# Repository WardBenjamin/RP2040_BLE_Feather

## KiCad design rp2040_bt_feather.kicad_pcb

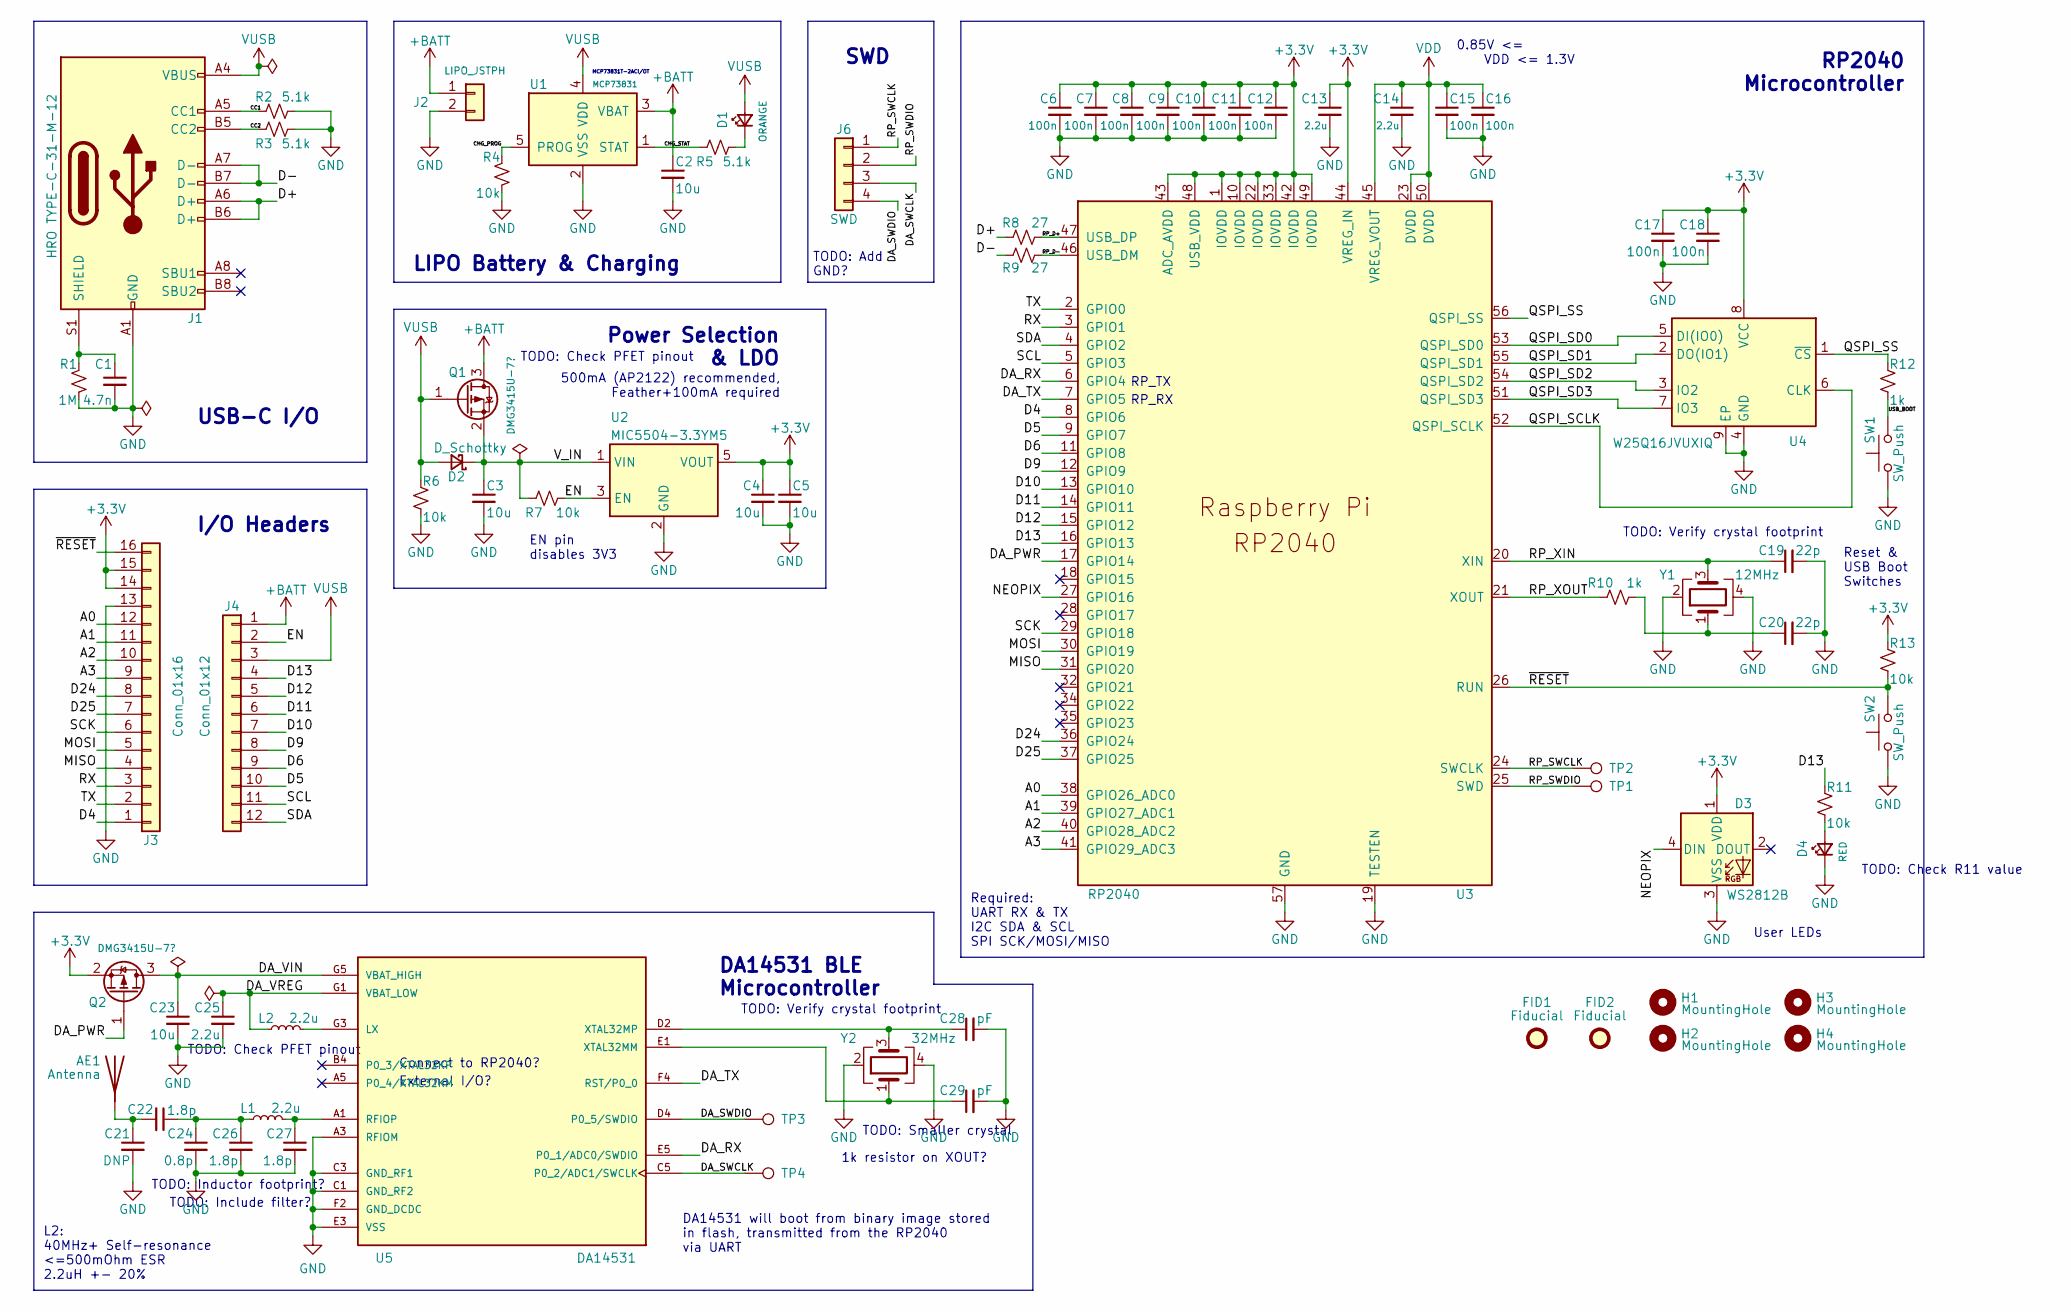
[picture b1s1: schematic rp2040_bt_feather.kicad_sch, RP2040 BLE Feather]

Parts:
AE1: Antenna
C1: 4.7n; C_0603_1608Metric
C2, C3, C4, C5: 10u; C_0805_2012Metric
C6, C7, C8, C9, C10, C11, C12, C15, C16, C17, C18: 100n; C_0603_1608Metric
C13, C14, C25: 2.2u; C_0603_1608Metric
C19, C20: 22p; C_0603_1608Metric
C21: DNP; C_0603_1608Metric
C22, C26, C27: 1.8p; C_0603_1608Metric
C23: 10u; C_0603_1608Metric
C24: 0.8p; C_0603_1608Metric
C28, C29: pF; C_0603_1608Metric
D1: ORANGE; D_0603_1608Metric; MPN ‎LTST-C190KFKT
D2: D_Schottky; D_SOD-123F
D3: WS2812B; LED_WS2812B_PLCC4_5.0x5.0mm_P3.2mm
D4: RED; D_0603_1608Metric
FID1, FID2: Fiducial; Fiducial_1mm_Mask2mm
H1, H2, H3, H4: MountingHole; MountingHole_2.5mm
J1: HRO TYPE-C-31-M-12; USB_C_Receptacle_HRO_TYPE-C-31-M-12
J2: LIPO_JSTPH; JST_PH_S2B-PH-SM4-TB_1x02-1MP_P2.00mm_Horizontal
J3: Conn_01x16; PinHeader_1x16_P2.54mm_Vertical
J4: Conn_01x12; PinHeader_1x12_P2.54mm_Vertical
J6: SWD; PinHeader_1x04_P2.54mm_Vertical
L1: 2.2u; L_0603_1608Metric
L2: 2.2u; L_0805_2012Metric
Q1, Q2: DMG3415U-7?; SOT-23
R1: 1M; R_0603_1608Metric
R2, R3, R5: 5.1k; R_0603_1608Metric
R4, R6, R7, R11, R13: 10k; R_0603_1608Metric
R8, R9: 27; R_0603_1608Metric
R10, R12: 1k; R_0603_1608Metric
SW1, SW2: SW_Push; SW_SPST_PTS830
TP1, TP3: SWDIO; TestPoint_THTPad_1.0x1.0mm_Drill0.5mm
TP2, TP4: SWCLK; TestPoint_THTPad_1.0x1.0mm_Drill0.5mm
U1: MCP73831; SOT-23-5; MPN MCP73831T-2ACI/OT
U2: MIC5504-3.3YM5; SOT-23-5
U3: RP2040; RP2040-QFN-56
U4: W25Q16JVUXIQ; WSON-8-1EP_6x5mm_P1.27mm_EP3.4x4.3mm
U5: DA14531; XCVR_DA14531-00000OG2; PARTREV 2.1
Y1: 12MHz; Crystal_SMD_2016-4Pin_2.0x1.6mm
Y2: 32MHz; Crystal_SMD_2016-4Pin_2.0x1.6mm; MPN ECS-320-8-37B-CKY-TR

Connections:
+3V3: C4.1, C5.1, C6.1, C7.1, C8.1, C9.1, C10.1, C11.1, C12.1, C13.1, C17.1, C18.1, D3.1 (VDD), J3.14, J3.15, Q2.2 (S), R13.1, U2.5 (VOUT), U3.1 (IOVDD), U3.10 (IOVDD), U3.22 (IOVDD), U3.33 (IOVDD), U3.42 (IOVDD), U3.43 (ADC_AVDD), U3.44 (VREG_IN), U3.48 (USB_VDD), U3.49 (IOVDD), U4.8 (VCC)
+BATT: C2.1, J2.1, J4.1, Q1.3 (D), U1.3 (VBAT)
/A0: J3.12, U3.38 (GPIO26_ADC0)
/A1: J3.11, U3.39 (GPIO27_ADC1)
/A2: J3.10, U3.40 (GPIO28_ADC2)
/A3: J3.9, U3.41 (GPIO29_ADC3)
/CC1: J1.A5 (CC1), R2.1
/CC2: J1.B5 (CC2), R3.1
/CHG_PROG: R4.1, U1.5 (PROG)
/CHG_STAT: R5.1, U1.1 (STAT)
/D4: J3.1, U3.8 (GPIO6)
/D5: J4.10, U3.9 (GPIO7)
/D6: J4.9, U3.11 (GPIO8)
/D9: J4.8, U3.12 (GPIO9)
/D10: J4.7, U3.13 (GPIO10)
/D11: J4.6, U3.14 (GPIO11)
/D12: J4.5, U3.15 (GPIO12)
/D13: J4.4, R11.1, U3.16 (GPIO13)
/D24: J3.8, U3.36 (GPIO24)
/D25: J3.7, U3.37 (GPIO25)
/D+: J1.A6 (D+), J1.B6 (D+), R8.1; also elsewhere on the board
/D-: J1.A7 (D-), J1.B7 (D-), R9.1; also elsewhere on the board
/DA_PWR: Q2.1 (G), U3.17 (GPIO14)
/DA_RX: U3.6 (GPIO4), U5.E5 (P0_1/ADC0/SWDIO)
/DA_SWCLK: J6.3, TP4.1, U5.C5 (P0_2/ADC1/SWCLK)
/DA_SWDIO: J6.4, TP3.1, U5.D4 (P0_5/SWDIO); also elsewhere on the board
/DA_TX: U3.7 (GPIO5), U5.F4 (RST/P0_0)
/DA_VIN: C23.1, Q2.3 (D), U5.G5 (VBAT_HIGH)
/DA_VREG: C25.1, L2.1, U5.G1 (VBAT_LOW)
/EN: J4.2, R7.2, U2.3 (EN)
/MISO: J3.4, U3.31 (GPIO20)
/MOSI: J3.5, U3.30 (GPIO19)
/NEOPIX: D3.4 (DIN), U3.27 (GPIO16)
/QSPI_SCLK: U3.52 (QSPI_SCLK), U4.6 (CLK)
/QSPI_SD0: U3.53 (QSPI_SD0), U4.5 (DI(IO0))
/QSPI_SD1: U3.55 (QSPI_SD1), U4.2 (DO(IO1))
/QSPI_SD2: U3.54 (QSPI_SD2), U4.3 (IO2)
/QSPI_SD3: U3.51 (QSPI_SD3), U4.7 (IO3)
/QSPI_SS: R12.1, U3.56 (QSPI_SS), U4.1 (~CS)
/RP_D+: R8.2, U3.47 (USB_DP)
/RP_D-: R9.2, U3.46 (USB_DM)
/RP_SWCLK: J6.1, TP2.1, U3.24 (SWCLK); also elsewhere on the board
/RP_SWDIO: J6.2, TP1.1, U3.25 (SWD); also elsewhere on the board
/RP_XIN: C19.1, U3.20 (XIN), Y1.3
/RP_XOUT: R10.1, U3.21 (XOUT)
/RX: J3.3, U3.3 (GPIO1)
/SCK: J3.6, U3.29 (GPIO18)
/SCL: J4.11, U3.5 (GPIO3)
/SDA: J4.12, U3.4 (GPIO2)
/TX: J3.2, U3.2 (GPIO0)
/USB_BOOT: R12.2, SW1.2
/V_IN: C3.1, D2.1 (K), Q1.2 (S), R7.1, U2.1 (VIN)
/~RESET: J3.16, R13.2, SW2.2, U3.26 (RUN)
GND: C1.2, C2.2, C3.2, C4.2, C5.2, C6.2, C7.2, C8.2, C9.2, C10.2, C11.2, C12.2, C13.2, C14.2, C15.2, C16.2, C17.2, C18.2, C19.2, C20.2, C21.2, C23.2, C24.2, C25.2, C26.2, C27.2, C28.2, C29.2, D3.3 (VSS), D4.1 (K), J1.A1 (GND), J1.A12 (GND), J1.B1 (GND), J1.B12 (GND), J2.2, J3.13, R1.2, R2.2, R3.2, R4.2, R6.2, SW1.1, SW2.1, U1.2 (VSS), U2.2 (GND), U3.19 (TESTEN), U3.57 (GND), U4.4 (GND), U4.9 (EP), U5.A3 (RFIOM), U5.C1 (GND_RF2), U5.C3 (GND_RF1), U5.E3 (VSS), U5.F2 (GND_DCDC), Y1.2, Y1.4, Y2.2, Y2.4
unnamed: AE1.1, C21.1, C22.2
unnamed: C1.1, J1.S1 (SHIELD), R1.1
unnamed: C20.1, R10.2, Y1.1
unnamed: C22.1, C24.1, C26.1, L1.1
unnamed: C27.1, L1.2, U5.A1 (RFIOP)
unnamed: C28.1, U5.D2 (XTAL32MP), Y2.3
unnamed: C29.1, U5.E1 (XTAL32MM), Y2.1
unnamed: D1.1 (K), R5.2
unnamed: D4.2 (A), R11.2
unnamed: L2.2, U5.G3 (LX)
VDD: C14.1, C15.1, C16.1, U3.23 (DVDD), U3.45 (VREG_VOUT), U3.50 (DVDD)
VUSB: D1.2 (A), D2.2 (A), J1.A4 (VBUS), J1.A9 (VBUS), J1.B4 (VBUS), J1.B9 (VBUS), J4.3, Q1.1 (G), R6.1, U1.4 (VDD)

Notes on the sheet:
L2: 40MHz+ Self-resonance <=500mOhm ESR 2.2uH +- 20%
TODO: Inductor footprint?
TODO: Include filter?
TODO: Check PFET pinout
USB-C I/O
I/O Headers
Connect to RP2040?
External I/O?
LIPO Battery & Charging
EN pin disables 3V3
MCP73831T-2ACI/OT
DA14531 will boot from binary image stored in flash, transmitted from the RP2040 via UART
DA14531 BLE Microcontroller
TODO: Verify crystal footprint
Power Selection & LDO
500mA (AP2122) recommended, Feather+100mA required
TODO: Add GND?
SWD
TODO: Smaller crystal
Required: UART RX & TX I2C SDA & SCL SPI SCK/MOSI/MISO
1k resistor on XOUT?
RP_TX
RP_RX
0.85V <= VDD <= 1.3V
User LEDs
Reset & USB Boot Switches
TODO: Check R11 value
RP2040 Microcontroller

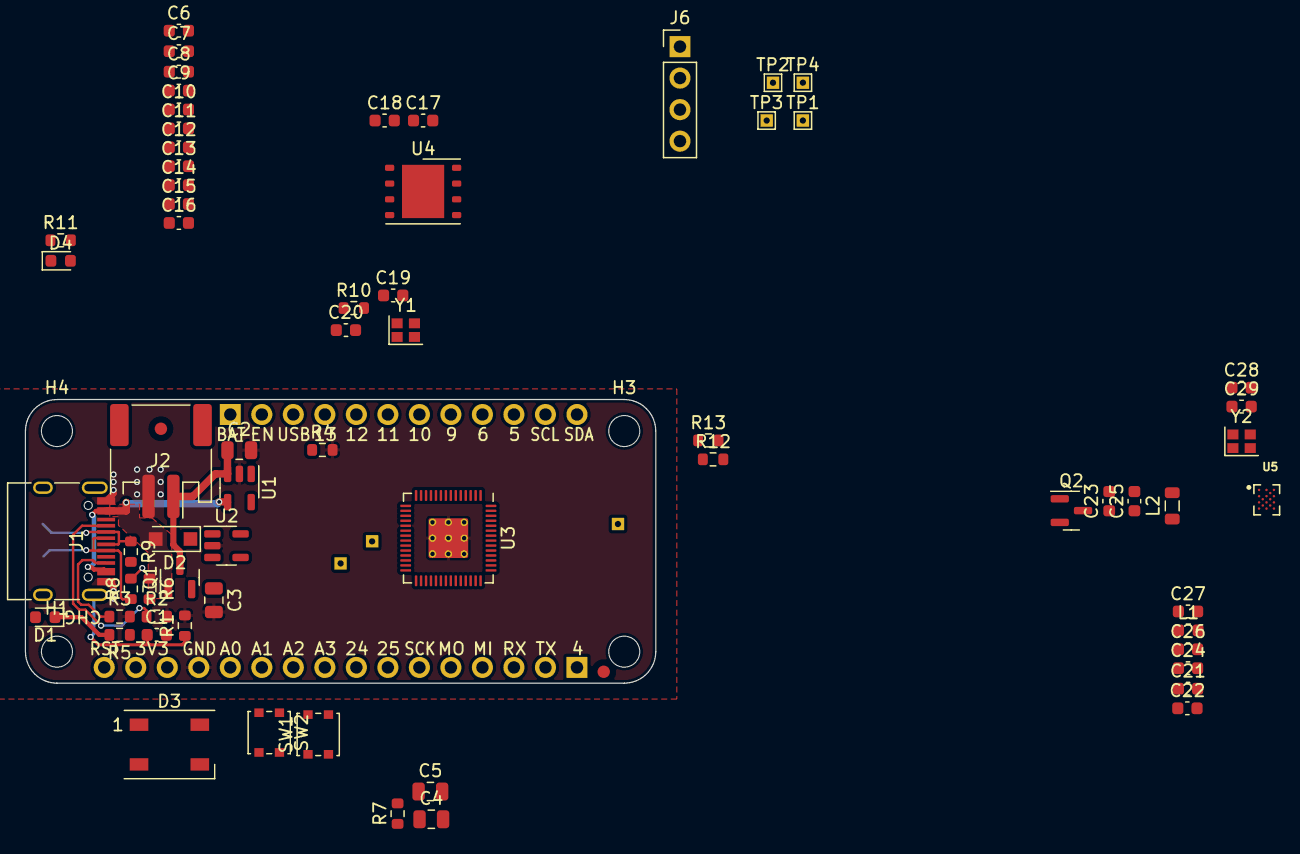
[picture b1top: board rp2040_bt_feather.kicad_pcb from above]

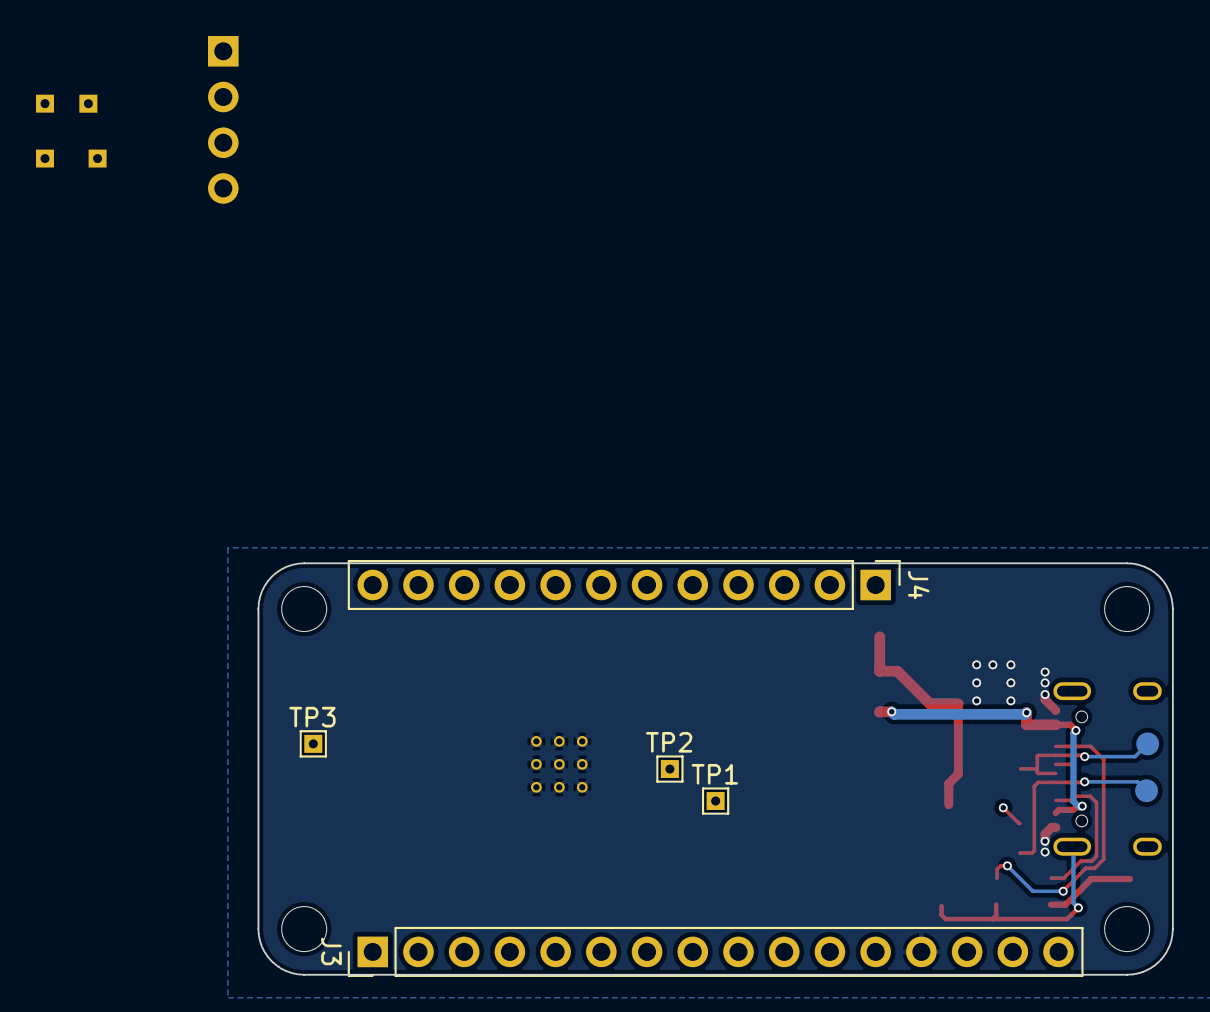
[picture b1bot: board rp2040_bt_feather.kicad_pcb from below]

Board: 2 copper layers, 50.8 x 22.9 mm, 79 parts (7 on the bottom side), 66 nets.

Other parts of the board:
D+1: TPB1,27; B1,27
D-1: TPB1,27; B1,27
TP1#2, TP3#2: SWDIO; TestPoint_THTPad_1.0x1.0mm_Drill0.5mm
TP2#2: SWCLK; TestPoint_THTPad_1.0x1.0mm_Drill0.5mm

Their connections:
/D+: D+1.TP; also elsewhere on the board
/D-: D-1.TP; also elsewhere on the board
/DA_SWDIO: TP3#2.1; also elsewhere on the board
/RP_SWCLK: TP2#2.1; also elsewhere on the board
/RP_SWDIO: TP1#2.1; also elsewhere on the board

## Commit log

2021-11-11 Lay out power input and supporting passives
